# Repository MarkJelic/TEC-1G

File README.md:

## File Links
| File | Description | Version |
|---|---|---|
| [Errata](./Errata.md) | <b>*CRITICAL:*</b> The latest Errata announcements. **Read BEFORE assembly!** | 2/jun/2024 |
| [Assembly Instructions](./Documentation/Assembly/Readme.md) | Instructions on putting the TEC-1G together | 0.2 |
| [Component Overlay](./TEC-1G_Component_Overlay_v1-21.pdf) | Searchable PDF for component placement. | 1.21 |
| [Parts List](./TEC-1G_PartsList_v1-5.pdf) | (Out of date. Needs updating. Use with caution. Always follow schematic.) | 1.5 |
| [BOM Sourcing](./files/TEC-1G_BOM_v1.5.xlsx) | (Out of date. Needs updating. Use with caution. Always follow schematic.) | 1.5 |
| [Schematic](./TEC-1G_Schematic_v1-22.pdf) | See what makes the TEC-1G tick. | 1.22 |
| [PCB Gerbers](./TEC-1G_Gerbers_v1-50_SigEd.zip) | Gerbers of the PCB so you can print your own! | 1.50 |
| [Monitors / ROMs](./ROMs/) | Download and burn the ROMs for your TEC-1G from this link! | 1.6 |
| [MON3 User Guide](./MON3_User_Guide_v1-6.pdf) | The comprehensive User Guide to MON3 | 1.6 |
| [TEC Deck](./TEC-Deck/) | The TEC Deck has multiple Cards that add major functionalityto the TEC-1G! | 1.2 |
| [GPIO Modules](./GPIO/) | See what modules can be attached to the GPIO connector on the LHS of the TEC-1G | 1.0 |
| [TEC Expander](./Expander/) | The Expander finally has the 8x8 LED Array... And it's in RGB! | 1.0 |

## News & Developments

We have added a new section to the GitHub that agregates all the news and new items for the TEC-1G. [Follow this link](https://github.com/MarkJelic/TEC-1G/tree/main/News) for all the latest info.

# TEC-1G Introduction

TEC-1G - A Z80 based single board computer.

The TEC-1G is a direct descendant of the Talking Electronics Computer, known as the TEC-1, which was first published by the Australian electronics hobbyist magazine ["Talking Electronics"](https://www.talkingelectronics.com/te_interactive_index.html) (or simply TE), between 1981 and 1991.

The TEC-1 was developed as a learning computer, designed to teach the basics of how a microprocessor works at the fundamental hardware and software level, and offered the ability to create and run simple programs in Z80 machine code. TE magazine covered the TEC-1 in six installments, known as "Issue 10" to "Issue 15". These magazines can be downloaded freely from the TEC-1 GitHub, located at [tec1group/TE-Magazines](https://github.com/tec1group/TE-Magazines)

Interest in the TEC-1 declined following the winding down of TE through the 1990's, which reflected a general decline in electronics as a hobby in Australia. This, coupled with interest in more advanced 'single chip' microcontrollers saw TEC-1's put aside and the world moved on.

The TEC-1 was revived around 2018 with a release of a reproduction PCB and related peripherals on the Internet. Retro computing has become quite popular of late, and so a an active TEC community has (re)formed through [Facebook](https://www.facebook.com/groups/tec1z80) with new hardware designs, enhanced versions and various expansion options being offered by various contributors within the community.

The 1G builds on both the TEC-1's base and recent history to modernize the overall design, address various design limitations and integrate many of the excellent add-ons into to a single PCB for the first time.

The TEC-1G remains true to the original TE design goals: it is is built using only simple through-hole TTL logic chips so it is easily built and understood by the hobbyist. For the first time, the TEC-1G will also be fully free and open source, in both its hardware and software. The TEC-1G is the ultimate TEC-1!

The 1G has been developed by Mark Jelic with the input of the original designers, John Hardy and Ken Stone, ex-TE staff member Craig Hart, along with contributions from community members Brian Chiha and Ian McLean. Finally, the 1G has also been produced with the blessing of Colin Mitchell, Talking Electronics owner.

## Major Features

- Full TEC-1 hardware and software compatability; runs all previous MONitors without modification
- Flexible memory options; 32K RAM, 16k ROM in default configuration. Up to 64k RAM + 16k ROM supported.
- Support for multiple configuration options and memory types from 2k to 32k memory devices
- RAM write protection for improved software development
- Shadow Memory and bank switching capabilities
- 20x4 LCD screen as primary display device
- Diagnostic & LED bar indicator for system state
- Z80A CPU running at 4.0MHz; 'slow' clock support for older monitors retained
- Full QWERTY MATRIX keyboard & joystick options
- Upgraded key options for onboard hex keypad; supports Gateron Low Profile switches with optional backlighting, as well as standard 12mm tactile buttons
- Improved RESET circuit for reliable start up and system stability
- USB B or 9-12v AC/DC power sources
- Serial interface using an optional FTDI/FT232 adaptor for USB communication with a PC or terminal
- Future support for SD card mass storage interface
- Native Z-80 expansion bus connectors supporting a full range of peripherals
- 'TEC-Deck' expansion connectors for future daughterboards
- 'TEC Expander' port for compatability with existing TEC peripherals
- HALT status LED

## More Documentation [Coming Soon™](/Documentation/readme.md)

I'd like to thank PCBWay for sponsoring the ongoing development of modules that are being added to the TEC-1G ecosystem. I'm impressed how proactive they are in finding projects like this one and encourage and foster such development. Thank you, PCBWay!

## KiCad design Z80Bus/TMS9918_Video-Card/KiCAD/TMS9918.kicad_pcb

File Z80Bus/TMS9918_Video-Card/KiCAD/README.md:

## KiCAD Design Files

The design is NOT quite finished. I have 3 traces to complete. When this is done, will release Gerbers so people can print their own boards.

Note that I (think) I have hardwired the Port Address to be something in the range that the Colecovision and SG-1000 which gives us a HUGE library of games to port if anyone cares to.

NONE of this has been tested! You are on your own, but of course the community would love to see it come to life and be able to run some ported games! Keep us in the loop. Happy to work together.

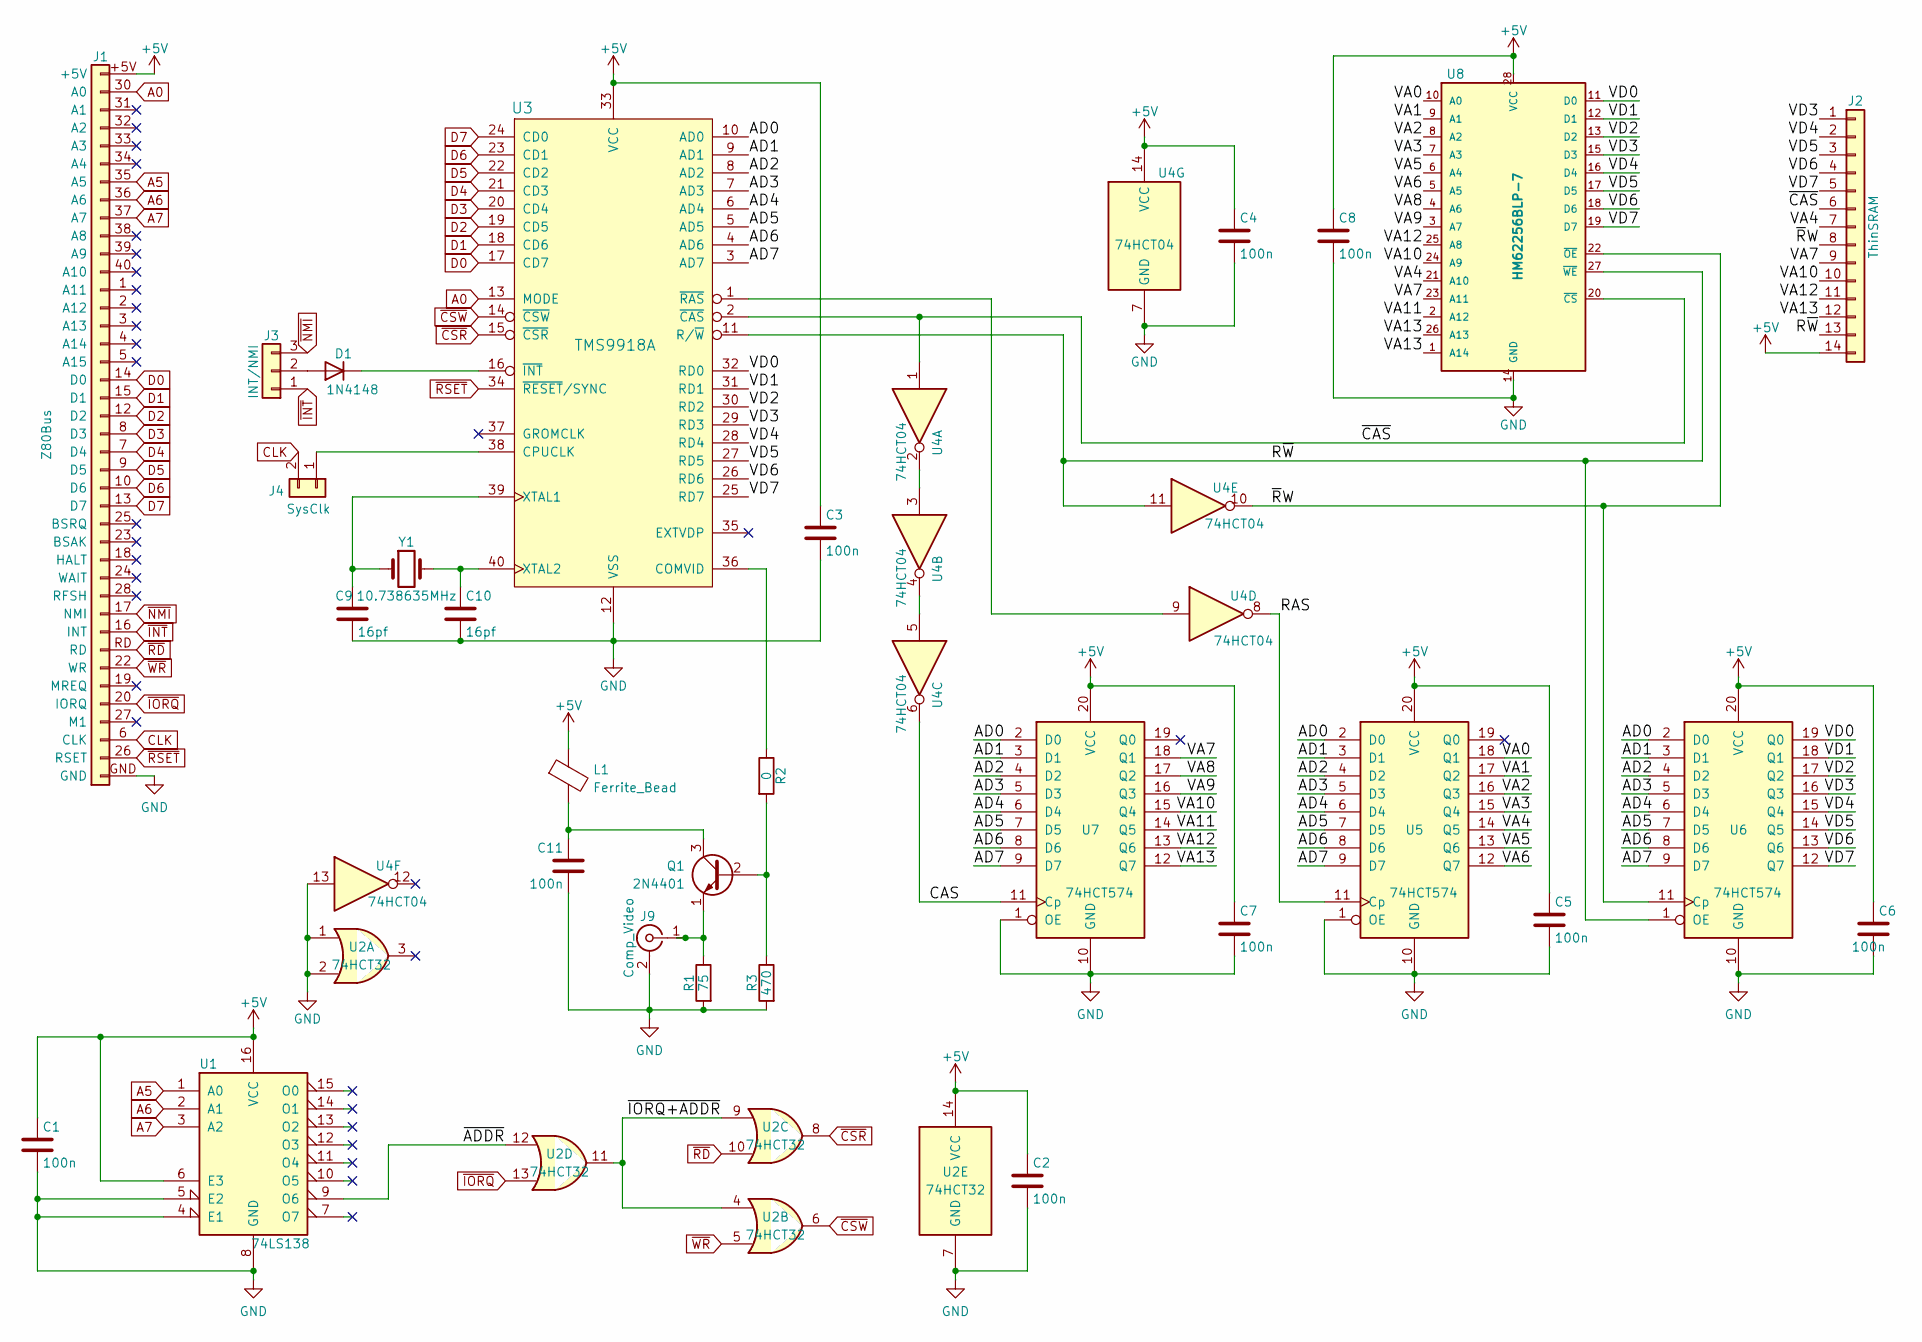
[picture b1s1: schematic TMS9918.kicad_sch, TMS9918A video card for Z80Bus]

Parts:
C1, C2, C3, C4, C5, C6, C7, C8, C11: 100n; C_Disc_D4.3mm_W1.9mm_P5.00mm
C9, C10: 16pf; C_Disc_D3.0mm_W1.6mm_P2.50mm
D1: 1N4148; D_DO-35_SOD27_P7.62mm_Horizontal
J1: Z80Bus; Z80Bus-Header_V+H_Plug
J2: ThinSRAM; PinHeader_1x14_P2.54mm_Vertical
J3: INT/NMI; PinHeader_1x03_P2.54mm_Vertical
J4: SysClk; PinHeader_1x02_P2.54mm_Vertical
J9: Comp_Video; RCA_Jack_RA
L1: Ferrite_Bead; R_Axial_DIN0207_L6.3mm_D2.5mm_P7.62mm_Horizontal
Q1: 2N4401; TO-92
R1: 75; R_Axial_DIN0207_L6.3mm_D2.5mm_P7.62mm_Horizontal
R2: 0; R_Axial_DIN0207_L6.3mm_D2.5mm_P7.62mm_Horizontal
R3: 470; R_Axial_DIN0207_L6.3mm_D2.5mm_P7.62mm_Horizontal
U1: 74LS138; DIP-16_W7.62mm_LongPads
U2: 74HCT32; DIP-14_W7.62mm_LongPads
U3: TMS9918A; DIP-40_W15.24mm_LongPads
U4: 74HCT04; DIP-14_W7.62mm_LongPads
U5, U6, U7: 74HCT574; DIP-20_W7.62mm_LongPads
U8: HM62256BLP-7; DIP-28_W15.24mm_LongPads
Y1: 10.738635MHz; Crystal_HC49-4H_Vertical

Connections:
+5V: C1.1, C2.1, C3.1, C4.1, C5.1, C6.1, C7.1, C8.1, J1.+5V, J2.14, L1.1, U1.6 (E3), U1.16 (VCC), U2.14 (VCC), U3.33 (VCC), U4.14 (VCC), U5.20 (VCC), U6.20 (VCC), U7.20 (VCC), U8.28 (VCC)
/AD0: U3.10 (AD0), U5.2 (D0), U6.2 (D0), U7.2 (D0)
/AD1: U3.9 (AD1), U5.3 (D1), U6.3 (D1), U7.3 (D1)
/AD2: U3.8 (AD2), U5.4 (D2), U6.4 (D2), U7.4 (D2)
/AD3: U3.7 (AD3), U5.5 (D3), U6.5 (D3), U7.5 (D3)
/AD4: U3.6 (AD4), U5.6 (D4), U6.6 (D4), U7.6 (D4)
/AD5: U3.5 (AD5), U5.7 (D5), U6.7 (D5), U7.7 (D5)
/AD6: U3.4 (AD6), U5.8 (D6), U6.8 (D6), U7.8 (D6)
/AD7: U3.3 (AD7), U5.9 (D7), U6.9 (D7), U7.9 (D7)
/CAS: U4.6, U7.11 (Cp)
/RAS: U4.8, U5.11 (Cp)
/R~W: J2.13, U3.11 (R/~W), U4.11, U6.1 (OE), U8.27 (~WE)
/VA0: U5.18 (Q1), U8.10 (A0)
/VA1: U5.17 (Q2), U8.9 (A1)
/VA2: U5.16 (Q3), U8.8 (A2)
/VA3: U5.15 (Q4), U8.7 (A3)
/VA4: J2.7, U5.14 (Q5), U8.21 (A10)
/VA5: U5.13 (Q6), U8.6 (A4)
/VA6: U5.12 (Q7), U8.5 (A5)
/VA7: J2.9, U7.18 (Q1), U8.23 (A11)
/VA8: U7.17 (Q2), U8.4 (A6)
/VA9: U7.16 (Q3), U8.3 (A7)
/VA10: J2.10, U7.15 (Q4), U8.24 (A9)
/VA11: U7.14 (Q5), U8.2 (A12)
/VA12: J2.11, U7.13 (Q6), U8.25 (A8)
/VA13: J2.12, U7.12 (Q7), U8.1 (A14), U8.26 (A13)
/VD0: U3.32 (RD0), U6.19 (Q0), U8.11 (D0)
/VD1: U3.31 (RD1), U6.18 (Q1), U8.12 (D1)
/VD2: U3.30 (RD2), U6.17 (Q2), U8.13 (D2)
/VD3: J2.1, U3.29 (RD3), U6.16 (Q3), U8.15 (D3)
/VD4: J2.2, U3.28 (RD4), U6.15 (Q4), U8.16 (D4)
/VD5: J2.3, U3.27 (RD5), U6.14 (Q5), U8.17 (D5)
/VD6: J2.4, U3.26 (RD6), U6.13 (Q6), U8.18 (D6)
/VD7: J2.5, U3.25 (RD7), U6.12 (Q7), U8.19 (D7)
/~ADDR: U1.9 (O6), U2.12
/~CAS: J2.6, U3.2 (~CAS), U4.1, U8.20 (~CS)
/~IORQ+ADDR: U2.4, U2.9, U2.11
/~RW: J2.8, U4.10, U6.11 (Cp), U8.22 (~OE)
A0: J1.30 (A0), U3.13 (MODE)
A5: J1.35 (A5), U1.1 (A0)
A6: J1.36 (A6), U1.2 (A1)
A7: J1.37 (A7), U1.3 (A2)
CLK: J1.6 (CLK), J4.2
D0: J1.14 (D0), U3.17 (CD7)
D1: J1.15 (D1), U3.18 (CD6)
D2: J1.12 (D2), U3.19 (CD5)
D3: J1.8 (D3), U3.20 (CD4)
D4: J1.7 (D4), U3.21 (CD3)
D5: J1.9 (D5), U3.22 (CD2)
D6: J1.10 (D6), U3.23 (CD1)
D7: J1.13 (D7), U3.24 (CD0)
GND: C1.2, C2.2, C3.2, C4.2, C5.2, C6.2, C7.2, C8.2, C9.2, C10.2, C11.2, J1.GND, J9.2 (Ext), R1.2, R3.2, U1.4 (E1), U1.5 (E2), U1.8 (GND), U2.1, U2.2, U2.7 (GND), U3.12 (VSS), U4.7 (GND), U4.13, U5.1 (OE), U5.10 (GND), U6.10 (GND), U7.1 (OE), U7.10 (GND), U8.14 (GND)
unnamed: C9.1, U3.39 (XTAL1), Y1.1
unnamed: C10.1, U3.40 (XTAL2), Y1.2
unnamed: C11.1, L1.2, Q1.3 (C)
unnamed: D1.1 (K), U3.16 (~INT)
unnamed: D1.2 (A), J3.2
unnamed: J4.1, U3.38 (CPUCLK)
unnamed: J9.1 (In), Q1.1 (E), R1.1
unnamed: Q1.2 (B), R2.2, R3.1
unnamed: R2.1, U3.36 (COMVID)
unnamed: U3.1 (~RAS), U4.9
unnamed: U4.2, U4.3
unnamed: U4.4, U4.5
~CSR: U2.8, U3.15 (~CSR)
~CSW: U2.6, U3.14 (~CSW)
~INT: J1.16 (INT), J3.1
~IORQ: J1.20 (IORQ), U2.13
~NMI: J1.17 (NMI), J3.3
~RD: J1.RD, U2.10
~RSET: J1.26 (RSET), U3.34 (~RESET/SYNC)
~WR: J1.22 (WR), U2.5

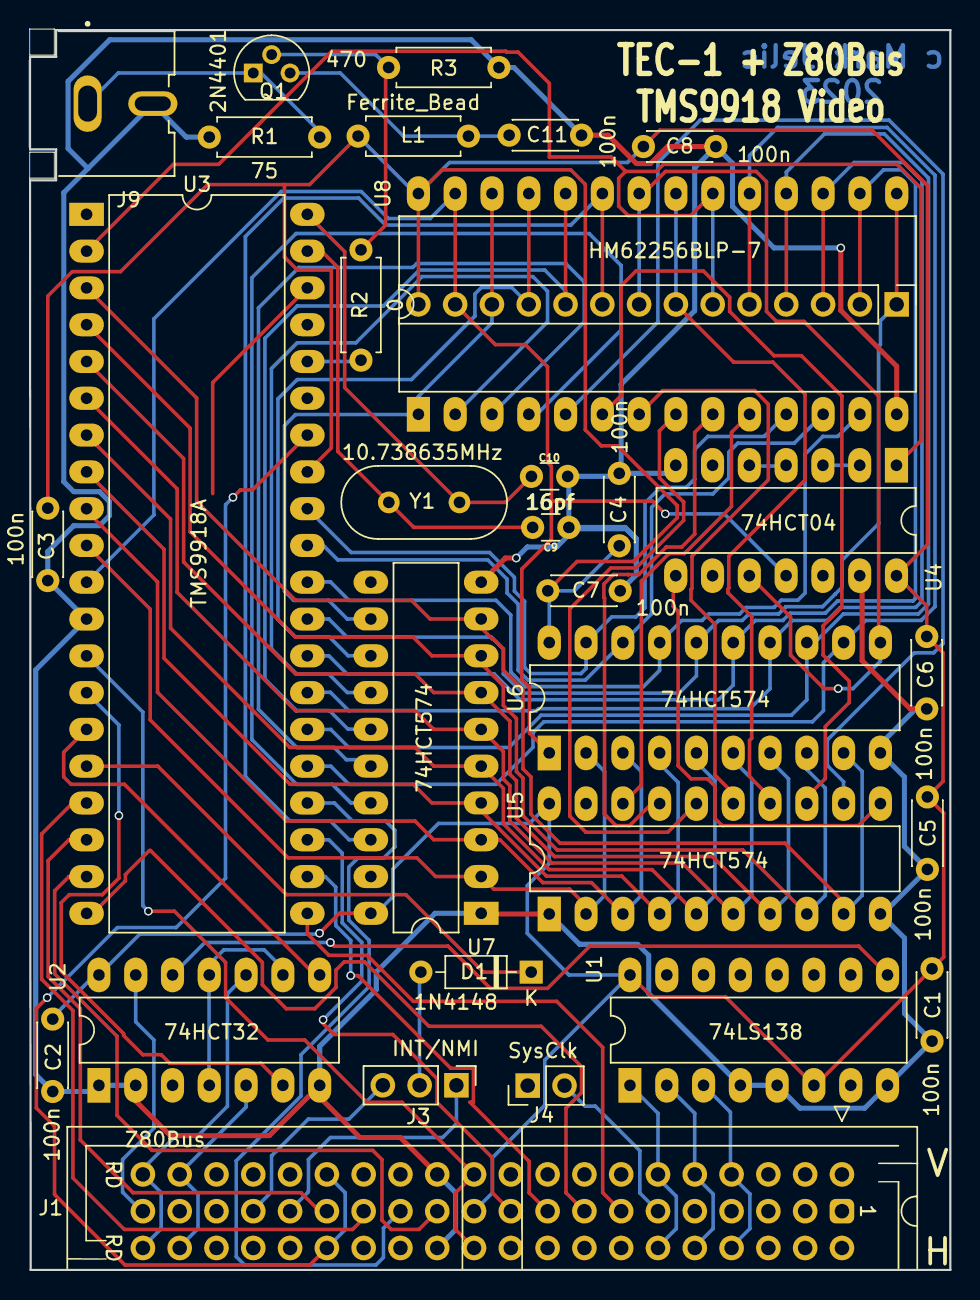
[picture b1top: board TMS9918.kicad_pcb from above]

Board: 2 copper layers, 63.5 x 85.6 mm, 31 parts (0 on the bottom side), 72 nets.

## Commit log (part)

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2023-12-27 sound.z80 version 1.0
2023-12-29 Monitor 3 v1.3 released
2023-12-29 Updated Version number to: BC23-13
    Version numbers to include the Author initials.
    Reason: A fork of the file may be created by Craig Hart, but might still be v1.3.
    Hence the Version number would be: CH23-13
2024-01-01 Upload Version 1.3
2024-01-07 Create releases
2024-01-23 Rename JamesE_TEC-1G-Stands_v10.stl to JamesE_TEC-1G-Stands_v1.stl
2024-01-23 Renamed file
2024-01-29 Tactile matrix keyboard frame
2024-03-22 mon3 1.3 Release
2024-03-22 readme updates
2024-05-05 FTDI Module - Defaults to 3.3v
2024-05-06 FRAM Readme
2024-05-06 FRAM Gerber Files
2024-06-01 Update Errata - Z80Bus Headers
    Z80Bus Headers supplied in the full kit. Silkscreen misleading.
2024-06-07 Mon3 v1.5 release
2024-06-07 remove old user guide
2024-06-08 Corrected the Version number of the ROM
2024-06-08 Corrected the ROM version number
    The format needs to be:
    NNNN.XX AAYY.VV
    NNNN is the name of the ROM. In this case, it is MON3
    XX is the target hardware. In this case, it is the 1G
    AA is the initials of the Author or Publisher. In this case, it is Brian Chiha, BC
    YY is the year of release. In this case it is 24
2024-06-08 Corrected the ROM version number (again)
    Must be in the format:
    NNNN.TT - AAYY.VV
    NNNN = Name
    TT = Target system
    AA = Author
    YY = Year
2024-06-08 Delete ROMs/MON3/source/past_releases directory
    This folder already exists off the MON3 root folder
2024-06-08 MON3 version 1.3 Source Files
2024-06-24 The TEC-1G Font
2024-08-24 Fitting the New Power Switch
2025-02-11 Add PATA TEC-Deck and 3D Case
2025-02-21 Schematic v1.2
2025-02-21 TEC-1G Schematic v1.21
2025-08-06 New version 1.6 MON3 Guide
2025-08-06 Corrected identifier
2025-08-06 Updated ROM images v1.6
2025-11-18 Schematic and Gerbers
2026-02-09 v1.5 of the PCB
2026-02-09 Gerber backups
2026-03-17 Delete ROMs/MON3/source/tmon.z80
    No longer inside MON3
2026-03-17 Delete ROMs/MON3/source/tiny_basic.z80
    No longer inside MON3
2026-03-18 Update release_notes.md
    Reversed the order of the release notes so the latest version is at the top of the file.
2026-03-19 Update Readme.md
    to be continued
2026-04-15 KiCAD Design Files
    *** UNFINISHED ***
    Still needs 3 traces routed. Updates to come.
2026-06-17 Add readme.md for sample code and demos
